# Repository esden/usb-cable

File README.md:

This repository contains random board designs related to USB cables.

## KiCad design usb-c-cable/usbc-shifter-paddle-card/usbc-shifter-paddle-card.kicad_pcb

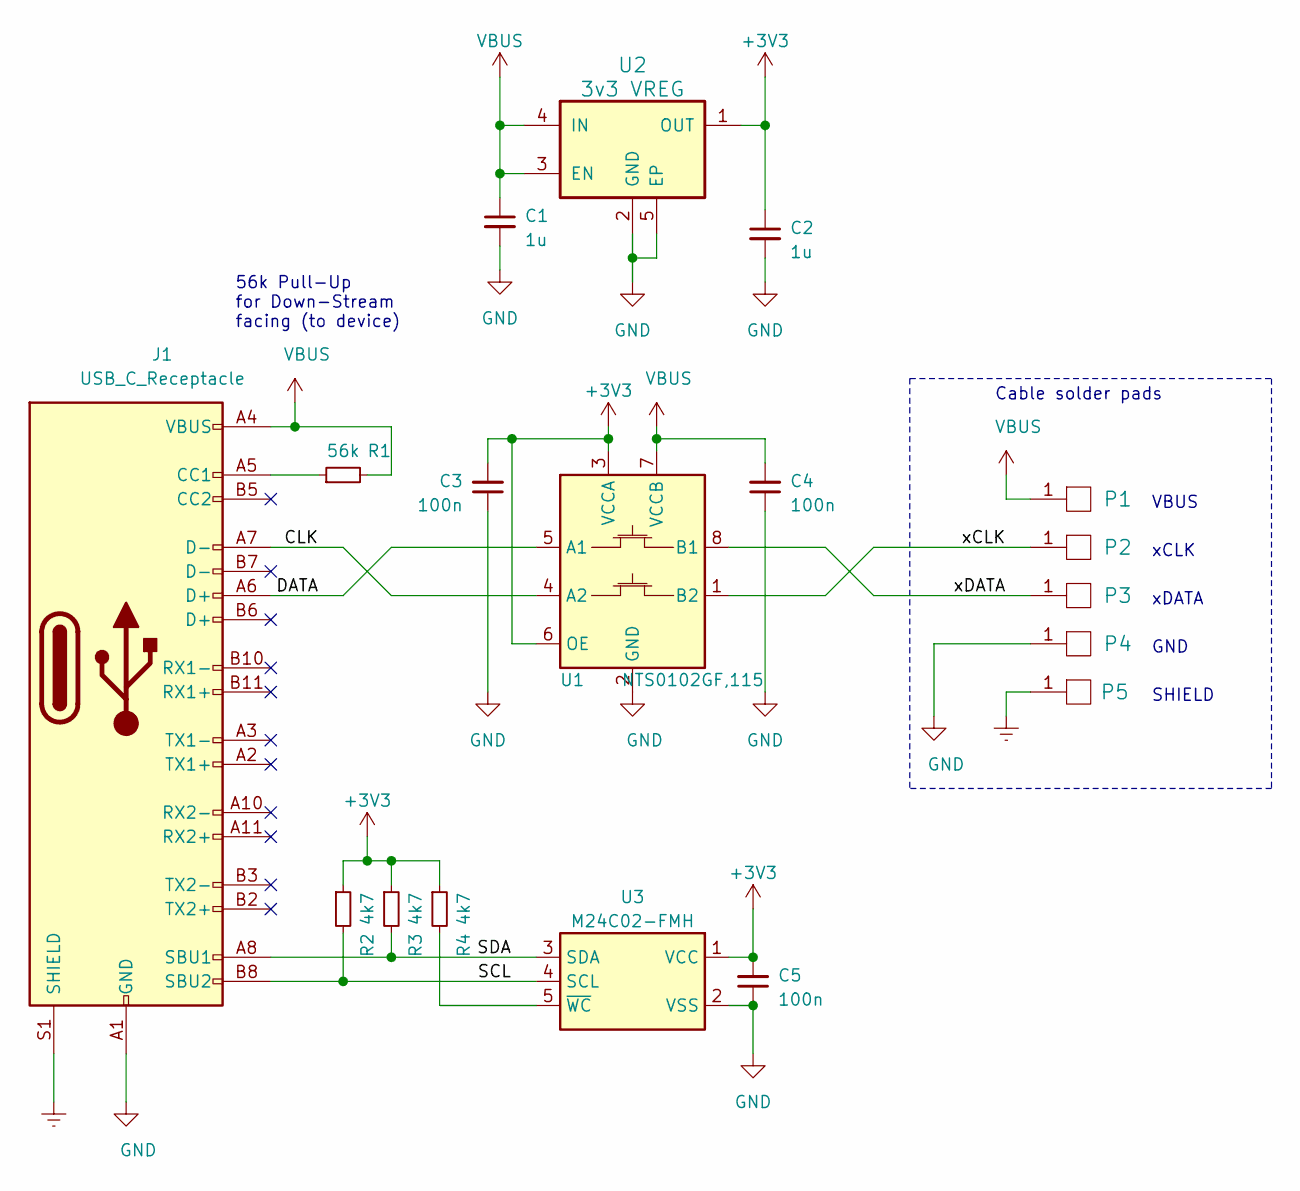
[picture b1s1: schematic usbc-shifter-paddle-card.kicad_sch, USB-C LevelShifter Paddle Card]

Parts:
C1, C2: 1u; C_0201
C3, C4, C5: 100n; C_0201
J1: USB_C_Receptacle; USB_C_Plug_CNC_C-AW10-AK5V50
P1, P2, P3, P4, P5: PAD_SMD; PAD_SMD_1.2x2.5
R1: 56k; R_0201
R2, R3, R4: 4k7; R_0201
U1: NTS0102GF,115; X2SON-8_1.4x1mm_P0.35mm
U2: 3v3 VREG; Texas_X2SON-4_1x1mm_P0.65mm
U3: M24C02-FMH; UFDFPN-5_1.7x1.4mm_P0.4mm

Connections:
+3V3: C2.1, C3.2, C5.2, R2.1, R3.1, R4.1, U1.3 (VCCA), U1.6 (OE), U2.1 (OUT), U3.1 (VCC)
/CLK: J1.A7 (D-), U1.4 (A2)
/DATA: J1.A6 (D+), U1.5 (A1)
/SCL: J1.B8 (SBU2), R2.2, U3.4 (SCL)
/SDA: J1.A8 (SBU1), R3.2, U3.3 (SDA)
/xCLK: P2.1 (PAD), U1.1 (B2)
/xDATA: P3.1 (PAD), U1.8 (B1)
Earth: J1.S1 (SHIELD), P5.1 (PAD)
GND: C1.2, C2.2, C3.1, C4.1, C5.1, J1.A1 (GND), J1.A12 (GND), J1.B1 (GND), J1.B12 (GND), P4.1 (PAD), U1.2 (GND), U2.2 (GND), U2.5 (EP), U3.2 (VSS)
unnamed: J1.A5 (CC1), R1.1
unnamed: R4.2, U3.5 (~WC)
VBUS: C1.1, C4.2, J1.A4 (VBUS), J1.A9 (VBUS), J1.B4 (VBUS), J1.B9 (VBUS), P1.1 (PAD), R1.2, U1.7 (VCCB), U2.3 (EN), U2.4 (IN)

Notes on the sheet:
56k Pull-Up for Down-Stream facing (to device)
Cable solder pads
VBUS
xCLK
xDATA
GND
SHIELD

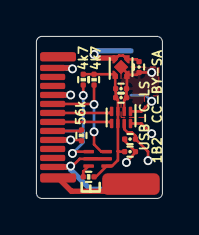
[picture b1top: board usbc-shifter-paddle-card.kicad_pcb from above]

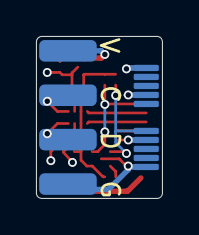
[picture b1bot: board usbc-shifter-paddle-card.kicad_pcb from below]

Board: 4 copper layers, 7.0 x 9.0 mm, 18 parts (4 on the bottom side), 12 nets.

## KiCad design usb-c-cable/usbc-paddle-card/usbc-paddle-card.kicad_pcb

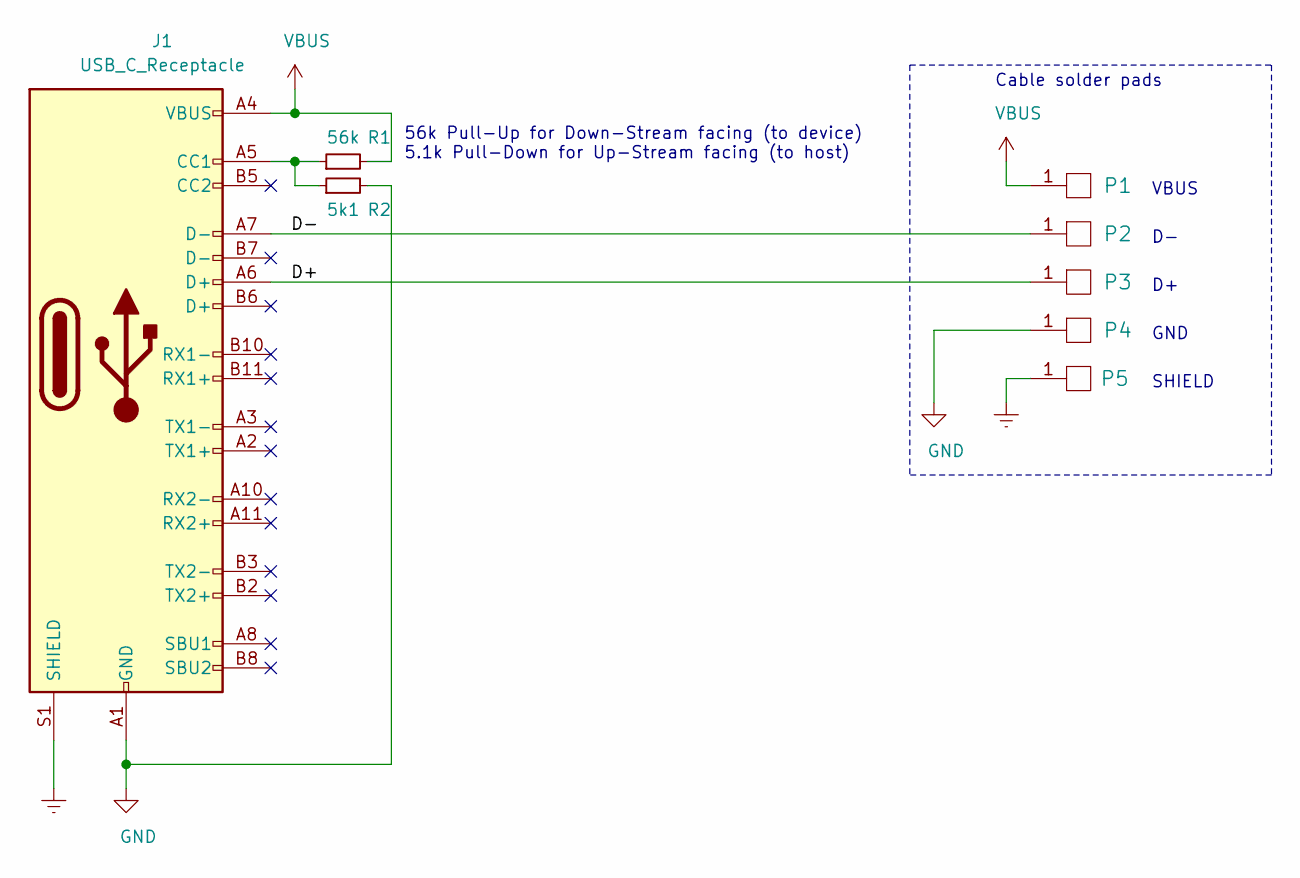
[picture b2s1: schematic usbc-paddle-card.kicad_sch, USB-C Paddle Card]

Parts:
J1: USB_C_Receptacle; USB_C_Plug_CNC_C-AW10-AK5V50
P1, P2, P3, P4, P5: PAD_SMD; PAD_SMD_1.2x2.5
R1: 56k; R_0402
R2: 5k1; R_0402

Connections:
/D+: J1.A6 (D+), P3.1 (PAD)
/D-: J1.A7 (D-), P2.1 (PAD)
Earth: J1.S1 (SHIELD), P5.1 (PAD)
GND: J1.A1 (GND), J1.A12 (GND), J1.B1 (GND), J1.B12 (GND), P4.1 (PAD), R2.2
unnamed: J1.A5 (CC1), R1.1, R2.1
VBUS: J1.A4 (VBUS), J1.A9 (VBUS), J1.B4 (VBUS), J1.B9 (VBUS), P1.1 (PAD), R1.2

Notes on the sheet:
56k Pull-Up for Down-Stream facing (to device) 5.1k Pull-Down for Up-Stream facing (to host)
Cable solder pads
VBUS
GND
SHIELD

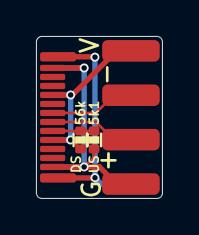
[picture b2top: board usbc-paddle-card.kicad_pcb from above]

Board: 2 copper layers, 7.0 x 9.0 mm, 8 parts (1 on the bottom side), 6 nets.

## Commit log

2020-11-18 Initial commit of the usb-c paddle card.
2020-11-18 Added readme.
2020-11-18 Added resistor value for up-stream facing paddle use.
2020-11-19 Added resistor for Up-Stream use.
2020-11-19 Added schematic PDF export.
2020-11-19 Added revision, copyright and license notes.
2021-04-06 Removed *.kicad_prl
2021-04-06 Added .gitignore.
2021-04-14 Updated PKL
2021-04-14 Initial commit of the level shifter paddle card.

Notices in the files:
usb-c-cable/usbc-paddle-card/usbc-paddle-card.kicad_pcb:
(C) 2020 1BitSquared
(C) 2020 Piotr Esden-Tempski
CC-BY-SA
usb-c-cable/usbc-paddle-card/usbc-paddle-card.kicad_sch:
License: CC-BY-SA 4.0
usb-c-cable/usbc-shifter-paddle-card/usbc-shifter-paddle-card.kicad_pcb:
(C) 2021 1BitSquared
(C) 2021 Piotr Esden-Tempski
1B2  CC-BY-SA
